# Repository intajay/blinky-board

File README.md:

## Blinky Board
Just another blinky board but Beautifully Designed

### Schematic

### Layout
Top Layer | Bottom Layer
------------ | -------------
 | 

### 3D Preview

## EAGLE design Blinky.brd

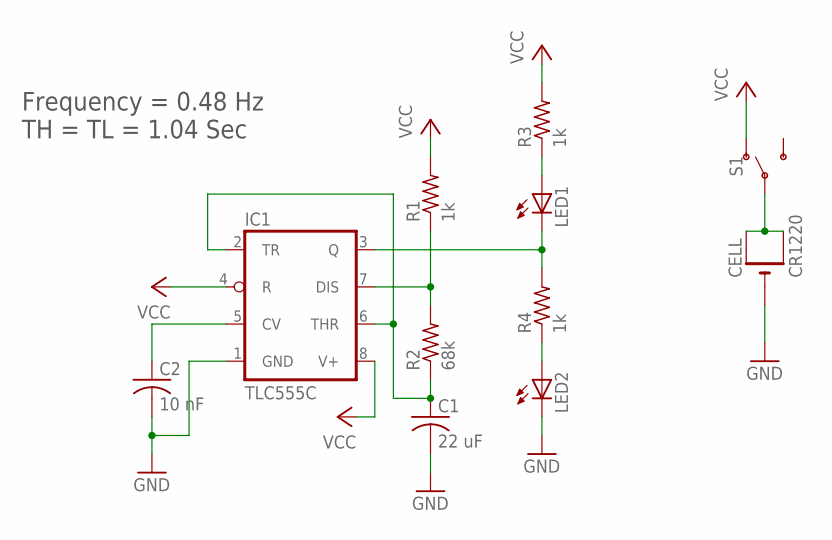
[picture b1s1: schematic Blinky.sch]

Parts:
C1: 22 uF; C1206
C2: 10 nF; C1206
CELL: CR1220; CR1220-SMD
IC1: TLC555C; SO08
LED1, LED2: LEDCHIPLED_1206; CHIPLED_1206
R1, R3, R4: 1k; R1206
R2: 68k; R1206
S1: SWITCH-SPDT-SMD-RIGHT-ANGLE; SWITCH_SPST_SMD_A

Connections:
GND: C1.2, C2.2, CELL.-, IC1.1 (GND), LED2.C
unnamed: C2.1, IC1.5 (CV)
unnamed: IC1.7 (DIS), R1.1, R2.2
unnamed: C1.1, IC1.2 (TR), IC1.6 (THR), R2.1
unnamed: CELL.+$1 (+), CELL.+$2 (+1), S1.2
unnamed: LED1.A, R3.1
unnamed: IC1.3 (Q), LED1.C, R4.2
unnamed: LED2.A, R4.1
VCC: IC1.4 (R), IC1.8 (V+), R1.2, R3.2, S1.1 (O)

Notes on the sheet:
Frequency = 0.48 Hz TH = TL = 1.04 Sec

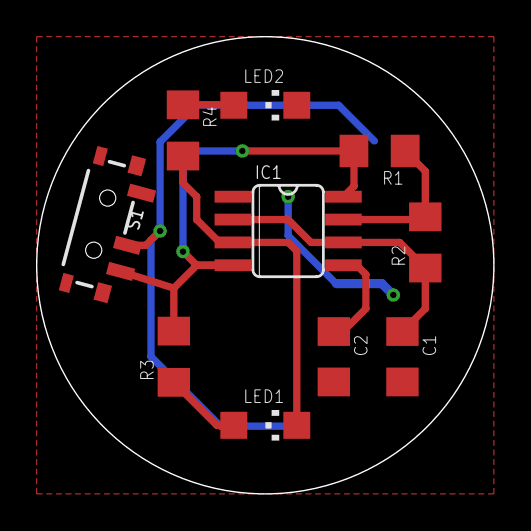
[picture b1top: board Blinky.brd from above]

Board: 2 copper layers, 25.4 x 25.4 mm, 11 parts (1 on the bottom side), 9 nets.

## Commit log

2017-09-23 Init
2017-09-23 Updated layout images
2017-09-23 minor update
